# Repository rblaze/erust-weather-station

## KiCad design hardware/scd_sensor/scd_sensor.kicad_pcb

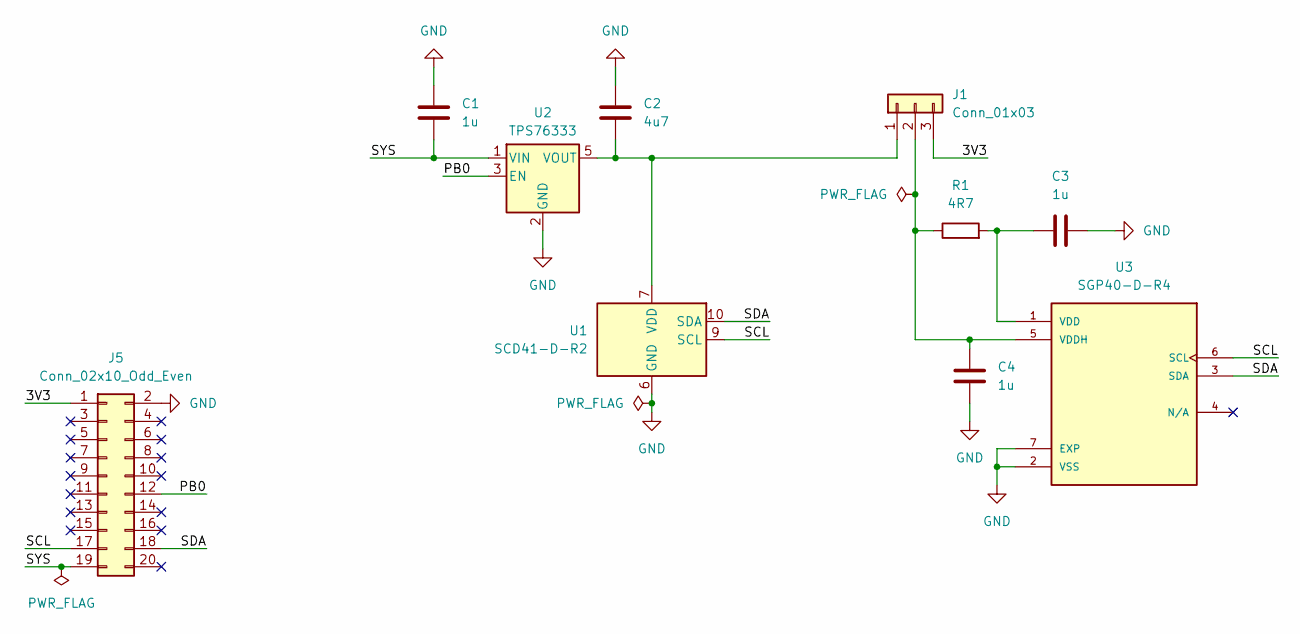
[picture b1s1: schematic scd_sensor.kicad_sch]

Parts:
C1, C3, C4: 1u; C_0402_1005Metric; JLCPCB C52923
C2: 4u7; C_0402_1005Metric; JLCPCB C23733
J1: Conn_01x03; PinHeader_1x03_P2.54mm_Vertical
J5: Conn_02x10_Odd_Even; PinHeader_2x10_P2.54mm_Vertical
R1: 4R7; R_0402_1005Metric; JLCPCB C23164
U1: SCD41-D-R2; Sensirion_SCD4x-1EP_10.1x10.1mm_P1.25mm_EP4.8x4.8mm; JLCPCB C3037696
U2: TPS76333; SOT-23-5
U3: SGP40-D-R4; XCDR_SGP40-D-R4; PARTREV 1.2; JLCPCB C2874215

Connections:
/3V3: J1.3, J5.1
/PB0: J5.12, U2.3 (EN)
/SCL: J5.17, U1.9 (SCL), U3.6 (SCL)
/SDA: J5.18, U1.10 (SDA), U3.3 (SDA)
/SYS: C1.2, J5.19, U2.1 (VIN)
GND: C1.1, C2.1, C3.2, C4.2, J5.2, U1.6 (GND), U1.20 (GND), U1.21 (GND), U2.2 (GND), U3.2 (VSS), U3.7 (EXP)
unnamed: C2.2, J1.1, U1.7 (VDD), U1.19 (VDD), U2.5 (VOUT)
unnamed: C4.1, J1.2, R1.1, U3.5 (VDDH)
unnamed: C3.1, R1.2, U3.1 (VDD)

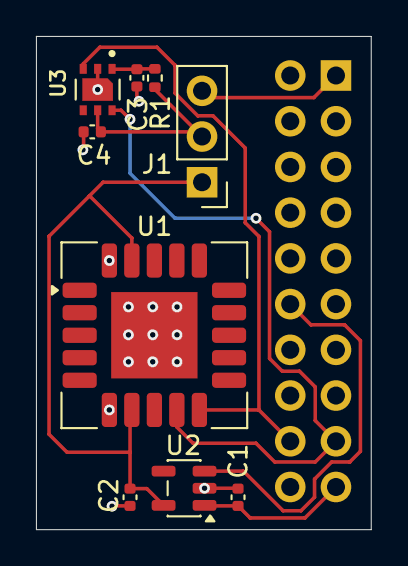
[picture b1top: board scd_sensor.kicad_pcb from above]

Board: 2 copper layers, 18.6 x 27.4 mm, 10 parts (1 on the bottom side), 9 nets.

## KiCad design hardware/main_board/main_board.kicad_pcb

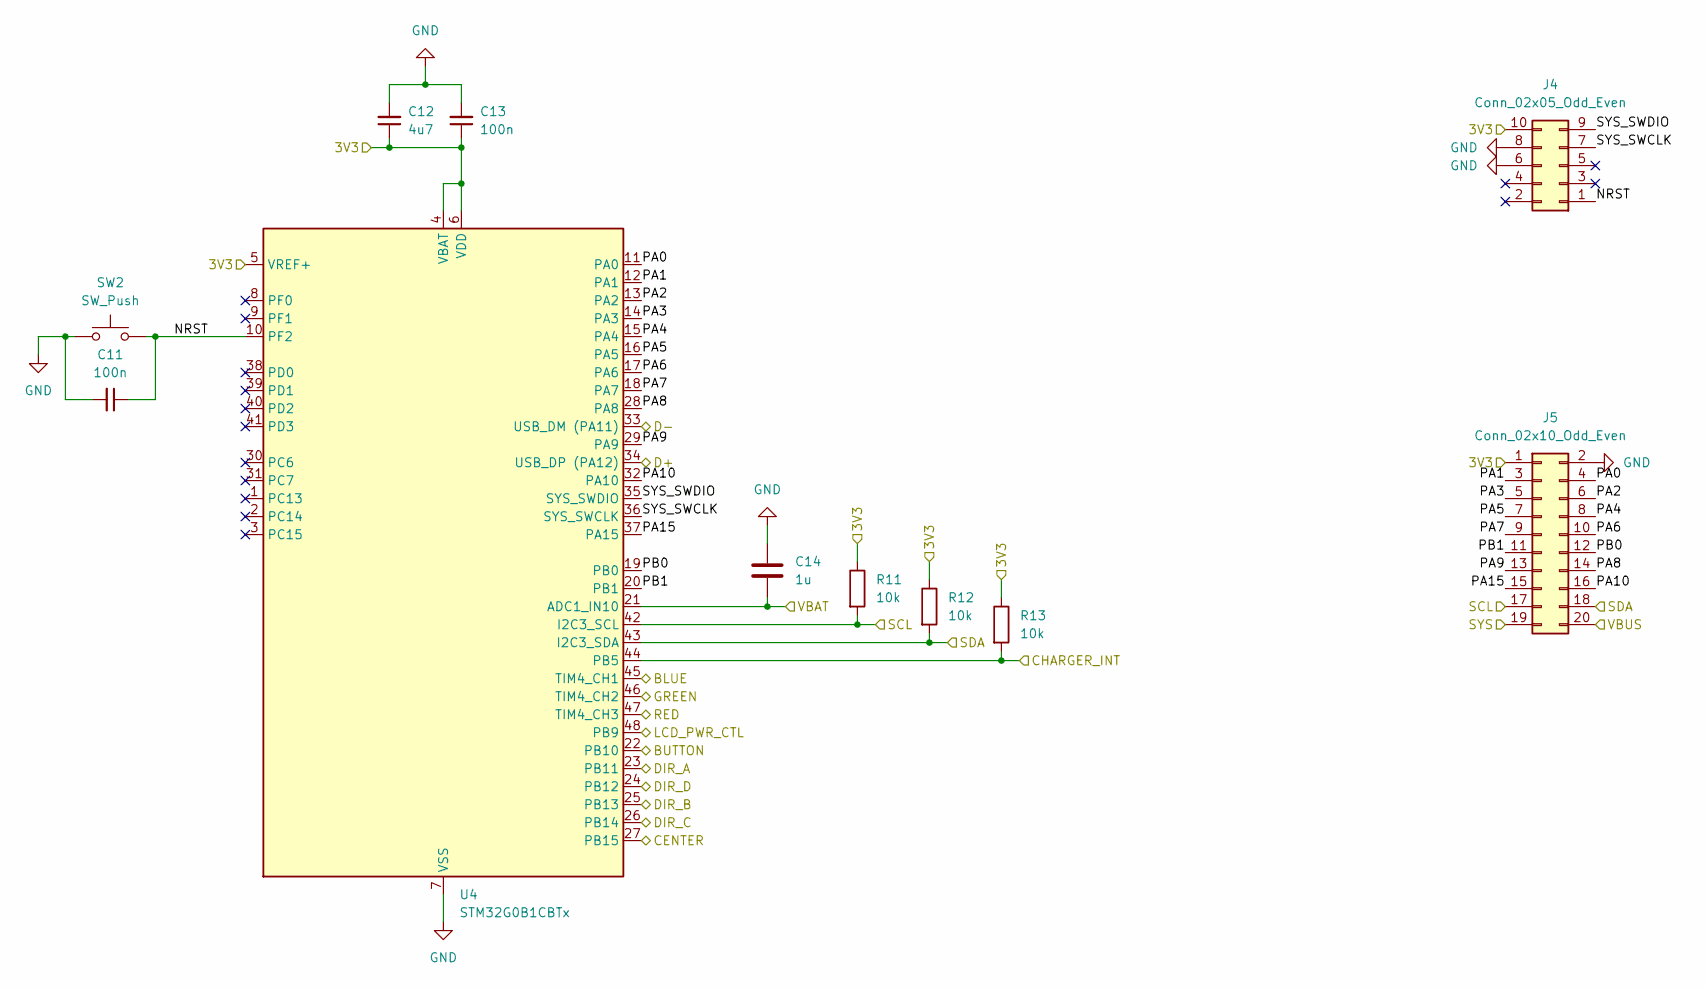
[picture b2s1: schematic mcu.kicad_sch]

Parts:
C11, C13: 100n; C_0402_1005Metric; JLCPCB C1525
C12: 4u7; C_0402_1005Metric; JLCPCB C23733
C14: 1u; C_0402_1005Metric; JLCPCB C52923
J4: Conn_02x05_Odd_Even; SAMTEC_FTSH-105-01-L-D-RA-K
J5: Conn_02x10_Odd_Even; SAMTEC_SSM-110-F-DH
R11, R12, R13: 10k; R_0402_1005Metric; JLCPCB C25744
SW2: SW_Push; SW_SPST_PTS810
U4: STM32G0B1CBTx; LQFP-48_7x7mm_P0.5mm; JLCPCB C2847904

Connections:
/MCU/3V3: C12.1, C13.1, J4.10, J5.1, R11.1, R12.1, R13.1, U4.4 (VBAT), U4.5 (VREF+), U4.6 (VDD); also elsewhere on the board
/MCU/BLUE: U4.45 (TIM4_CH1); also elsewhere on the board
/MCU/BUTTON: U4.22 (PB10); also elsewhere on the board
/MCU/CENTER: U4.27 (PB15); also elsewhere on the board
/MCU/CHARGER_INT: R13.2, U4.44 (PB5); also elsewhere on the board
/MCU/D+: U4.34 (USB_DP (PA12)); also elsewhere on the board
/MCU/D-: U4.33 (USB_DM (PA11)); also elsewhere on the board
/MCU/DIR_A: U4.23 (PB11); also elsewhere on the board
/MCU/DIR_B: U4.25 (PB13); also elsewhere on the board
/MCU/DIR_C: U4.26 (PB14); also elsewhere on the board
/MCU/DIR_D: U4.24 (PB12); also elsewhere on the board
/MCU/GREEN: U4.46 (TIM4_CH2); also elsewhere on the board
/MCU/LCD_PWR_CTL: U4.48 (PB9); also elsewhere on the board
/MCU/NRST: C11.1, J4.1, SW2.2, U4.10 (PF2)
/MCU/PA0: J5.4, U4.11 (PA0)
/MCU/PA1: J5.3, U4.12 (PA1)
/MCU/PA2: J5.6, U4.13 (PA2)
/MCU/PA3: J5.5, U4.14 (PA3)
/MCU/PA4: J5.8, U4.15 (PA4)
/MCU/PA5: J5.7, U4.16 (PA5)
/MCU/PA6: J5.10, U4.17 (PA6)
/MCU/PA7: J5.9, U4.18 (PA7)
/MCU/PA8: J5.14, U4.28 (PA8)
/MCU/PA9: J5.13, U4.29 (PA9)
/MCU/PA10: J5.16, U4.32 (PA10)
/MCU/PA15: J5.15, U4.37 (PA15)
/MCU/PB0: J5.12, U4.19 (PB0)
/MCU/PB1: J5.11, U4.20 (PB1)
/MCU/RED: U4.47 (TIM4_CH3); also elsewhere on the board
/MCU/SCL: J5.17, R11.2, U4.42 (I2C3_SCL); also elsewhere on the board
/MCU/SDA: J5.18, R12.2, U4.43 (I2C3_SDA); also elsewhere on the board
/MCU/SYS_SWCLK: J4.7, U4.36 (SYS_SWCLK)
/MCU/SYS_SWDIO: J4.9, U4.35 (SYS_SWDIO)
/MCU/VBAT: C14.2, U4.21 (ADC1_IN10); also elsewhere on the board
/MCU/VBUS: J5.20; also elsewhere on the board
/Power/SYS: J5.19; also elsewhere on the board
GND: C11.2, C12.2, C13.2, C14.1, J4.6, J4.8, J5.2, SW2.1, U4.7 (VSS); also elsewhere on the board

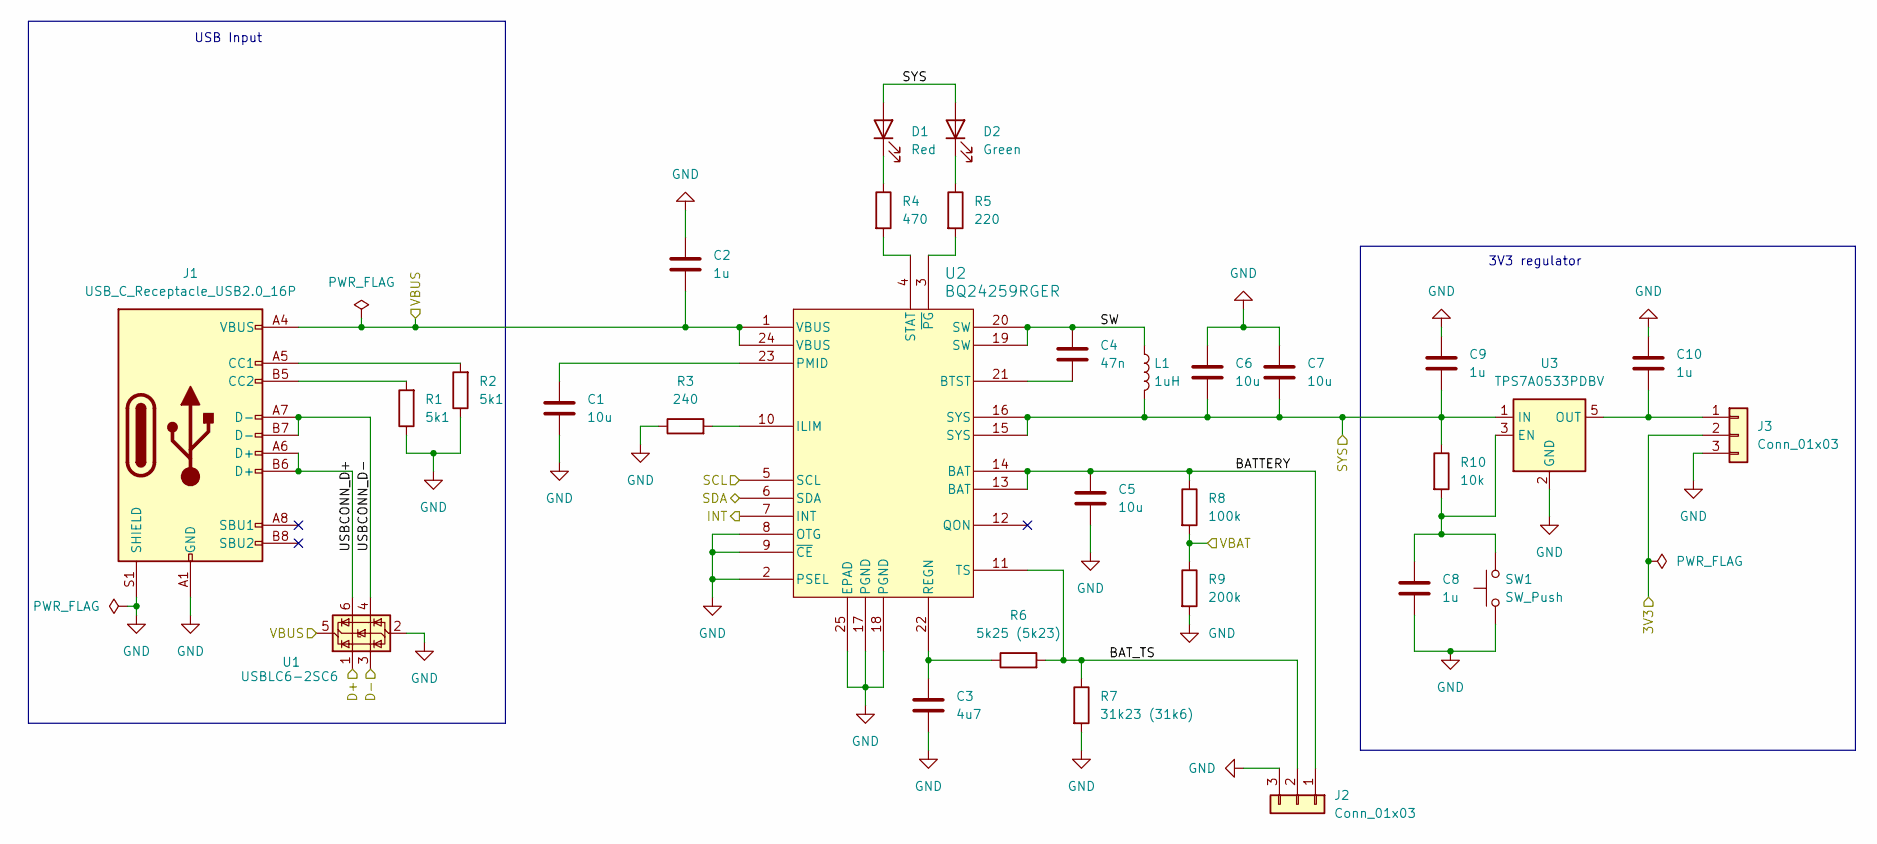
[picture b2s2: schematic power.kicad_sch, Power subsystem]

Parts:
C1, C5, C6, C7: 10u; C_0603_1608Metric; JLCPCB C19702
C2, C8, C9, C10: 1u; C_0402_1005Metric; JLCPCB C52923
C3: 4u7; C_0402_1005Metric; JLCPCB C23733
C4: 47n; C_0402_1005Metric; JLCPCB C384812
D1: Red; LED_0805_2012Metric; JLCPCB C2286
D2: Green; LED_0805_2012Metric; JLCPCB C72043
J1: USB_C_Receptacle_USB2.0_16P; USB_C_Receptacle_GCT_USB4105-xx-A_16P_TopMnt_Horizontal; JLCPCB C165948
J2: Conn_01x03; JST_PH_S3B-PH-SM4-TB_1x03-1MP_P2.00mm_Horizontal
J3: Conn_01x03; Harwin_M20-89003xx_1x03_P2.54mm_Horizontal
L1: 1uH; L_Murata_DFE201610P; JLCPCB C161082
R1, R2: 5k1; R_0402_1005Metric; JLCPCB C25905
R3: 240; R_0402_1005Metric; JLCPCB C25091
R4: 470; R_0402_1005Metric; JLCPCB C25117
R5: 220; R_0402_1005Metric; JLCPCB C25091
R6: 5k25 (5k23); R_0402_1005Metric; JLCPCB C852857
R7: 31k23 (31k6); R_0402_1005Metric; JLCPCB C852720
R8: 100k; R_0402_1005Metric; JLCPCB C25741
R9: 200k; R_0402_1005Metric; JLCPCB C25764
R10: 10k; R_0402_1005Metric; JLCPCB C25744
SW1: SW_Push; SW_SPST_PTS810
U1: USBLC6-2SC6; SOT-23-6; JLCPCB C7519
U2: BQ24259RGER; RGE24_2P7X2P7_TEX; JLCPCB C473366
U3: TPS7A0533PDBV; SOT-23-5; JLCPCB C2862740

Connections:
/MCU/3V3: J3.2; also elsewhere on the board
/MCU/CHARGER_INT: U2.7 (INT); also elsewhere on the board
/MCU/D+: U1.1 (I/O1); also elsewhere on the board
/MCU/D-: U1.3 (I/O2); also elsewhere on the board
/MCU/SCL: U2.5 (SCL); also elsewhere on the board
/MCU/SDA: U2.6 (SDA); also elsewhere on the board
/MCU/VBAT: R8.2, R9.1; also elsewhere on the board
/MCU/VBUS: C2.2, J1.A4 (VBUS), J1.A9 (VBUS), J1.B4 (VBUS), J1.B9 (VBUS), U1.5 (VBUS), U2.1 (VBUS), U2.24 (VBUS); also elsewhere on the board
/Power/BATTERY: C5.1, J2.1, R8.1, U2.13 (BAT), U2.14 (BAT)
/Power/BAT_TS: J2.2, R6.2, R7.1, U2.11 (TS)
/Power/SW: C4.1, L1.1, U2.19 (SW), U2.20 (SW)
/Power/SYS: C6.2, C7.2, C9.2, D1.2 (A), D2.2 (A), L1.2, R10.1, U2.15 (SYS), U2.16 (SYS), U3.1 (IN); also elsewhere on the board
/Power/USBCONN_D+: J1.A6 (D+), J1.B6 (D+), U1.6 (I/O1)
/Power/USBCONN_D-: J1.A7 (D-), J1.B7 (D-), U1.4 (I/O2)
GND: C1.2, C2.1, C3.2, C5.2, C6.1, C7.1, C8.2, C9.1, C10.1, J1.A1 (GND), J1.A12 (GND), J1.B1 (GND), J1.B12 (GND), J1.S1 (SHIELD), J2.3, J3.3, R1.1, R2.1, R3.1, R7.2, R9.2, SW1.1, U1.2 (GND), U2.2 (PSEL), U2.8 (OTG), U2.9 (~CE), U2.17 (PGND), U2.18 (PGND), U2.25 (EPAD), U2.V, U3.2 (GND); also elsewhere on the board
unnamed: D1.1 (K), R4.1
unnamed: D2.1 (K), R5.1
unnamed: J1.A5 (CC1), R2.2
unnamed: J1.B5 (CC2), R1.2
unnamed: C10.2, J3.1, U3.5 (OUT)
unnamed: C4.2, U2.21 (BTST)
unnamed: R3.2, U2.10 (ILIM)
unnamed: C1.1, U2.23 (PMID)
unnamed: C3.1, R6.1, U2.22 (REGN)
unnamed: R4.2, U2.4 (STAT)
unnamed: R5.2, U2.3 (~PG)
unnamed: C8.1, R10.2, SW1.2, U3.3 (EN)

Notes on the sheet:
3V3 regulator
USB Input

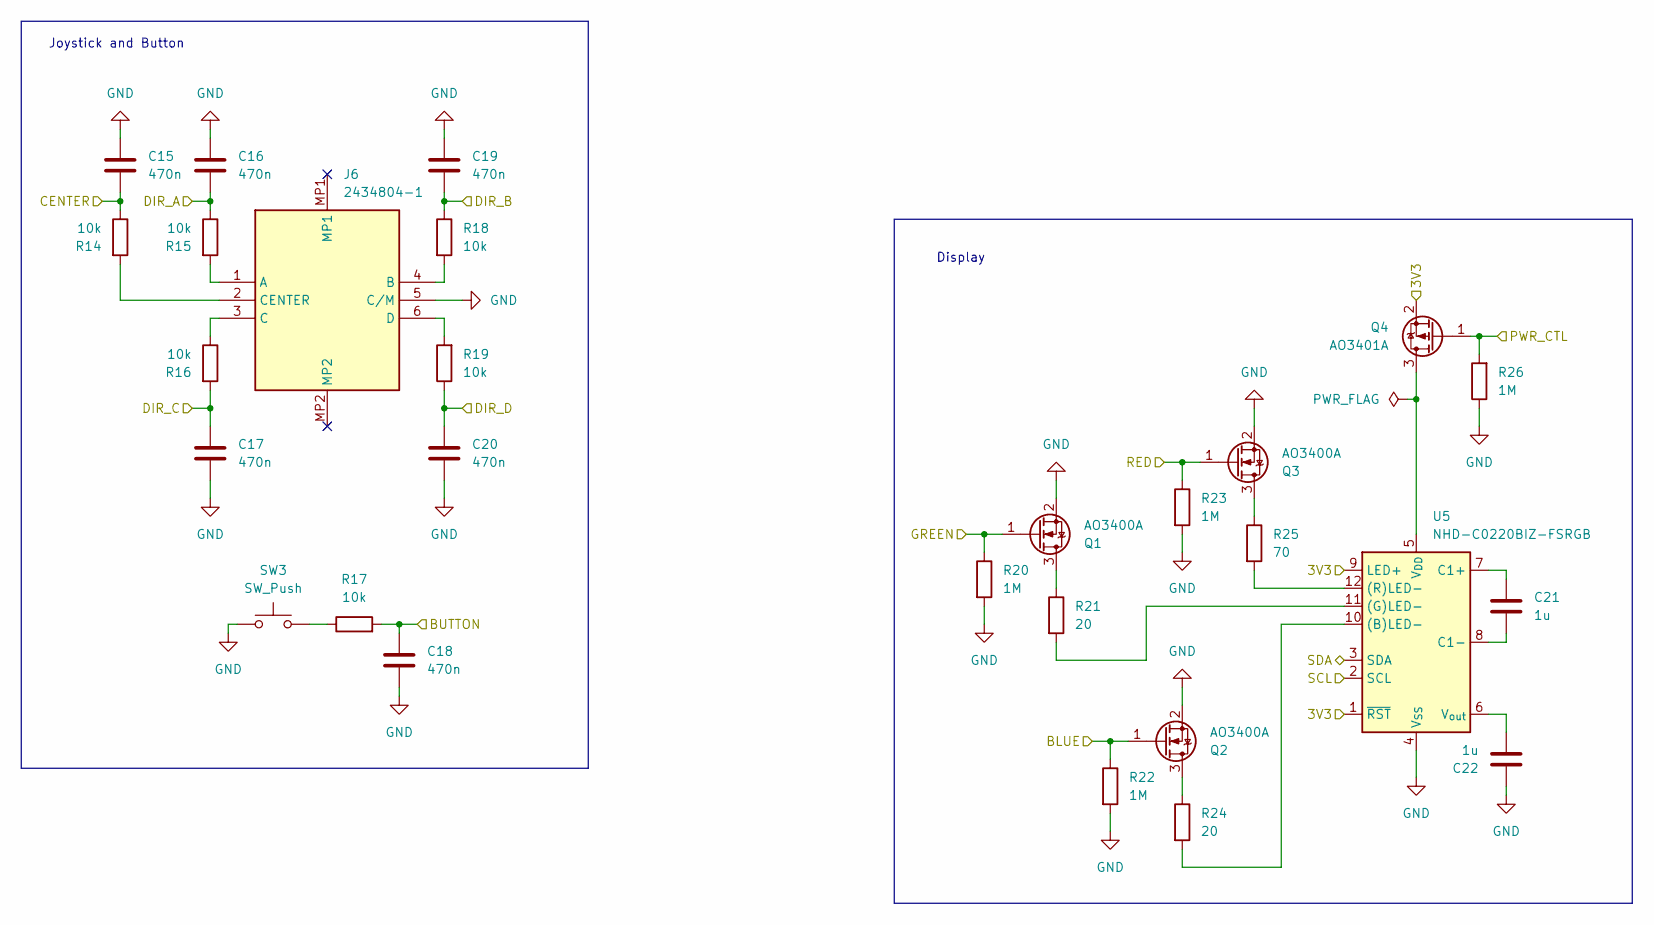
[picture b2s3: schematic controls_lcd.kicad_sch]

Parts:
C15, C16, C17, C18, C19, C20: 470n; C_0402_1005Metric; JLCPCB C47339
C21, C22: 1u; C_0402_1005Metric; JLCPCB C52923
J6: 2434804-1; TE_24348041; Manufacturer_Part_Number 2434804-1
Q1, Q2, Q3: AO3400A; SOT-23; JLCPCB C22469448
Q4: AO3401A; SOT-23; JLCPCB C28646269
R14, R15, R16, R17, R18, R19: 10k; R_0402_1005Metric; JLCPCB C25744
R20, R22, R23, R26: 1M; R_0402_1005Metric; JLCPCB C26083
R21, R24: 20; R_0402_1005Metric; JLCPCB C25092
R25: 70; R_0402_1005Metric; JLCPCB C25133
SW3: SW_Push; SW_SPST_PTS810
U5: NHD-C0220BIZ-FSRGB; NHD-C0220BiZ-FSRGB_no_mount

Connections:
/MCU/3V3: Q4.2 (S), U5.1 (~RST), U5.9 (LED+); also elsewhere on the board
/MCU/BLUE: Q2.1 (G), R22.1; also elsewhere on the board
/MCU/BUTTON: C18.1, R17.2; also elsewhere on the board
/MCU/CENTER: C15.1, R14.1; also elsewhere on the board
/MCU/DIR_A: C16.1, R15.1; also elsewhere on the board
/MCU/DIR_B: C19.1, R18.1; also elsewhere on the board
/MCU/DIR_C: C17.2, R16.2; also elsewhere on the board
/MCU/DIR_D: C20.2, R19.1; also elsewhere on the board
/MCU/GREEN: Q1.1 (G), R20.1; also elsewhere on the board
/MCU/LCD_PWR_CTL: Q4.1 (G), R26.2; also elsewhere on the board
/MCU/RED: Q3.1 (G), R23.1; also elsewhere on the board
/MCU/SCL: U5.2 (SCL); also elsewhere on the board
/MCU/SDA: U5.3 (SDA); also elsewhere on the board
GND: C15.2, C16.2, C17.1, C18.2, C19.2, C20.1, C22.1, J6.5 (C/M), Q1.2 (S), Q2.2 (S), Q3.2 (S), R20.2, R22.2, R23.2, R26.1, SW3.2, U5.4 (V_{SS}); also elsewhere on the board
unnamed: J6.1 (A), R15.2
unnamed: J6.4 (B), R18.2
unnamed: J6.3 (C), R16.1
unnamed: J6.2 (CENTER), R14.2
unnamed: J6.6 (D), R19.2
unnamed: Q1.3 (D), R21.1
unnamed: Q2.3 (D), R24.1
unnamed: Q3.3 (D), R25.1
unnamed: Q4.3 (D), U5.5 (V_{DD})
unnamed: R17.1, SW3.1
unnamed: R24.2, U5.10 ((B)LED-)
unnamed: R21.2, U5.11 ((G)LED-)
unnamed: R25.2, U5.12 ((R)LED-)
unnamed: C21.1, U5.7 (C1+)
unnamed: C21.2, U5.8 (C1-)
unnamed: C22.2, U5.6 (V_{out})

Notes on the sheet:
Display
Joystick and Button

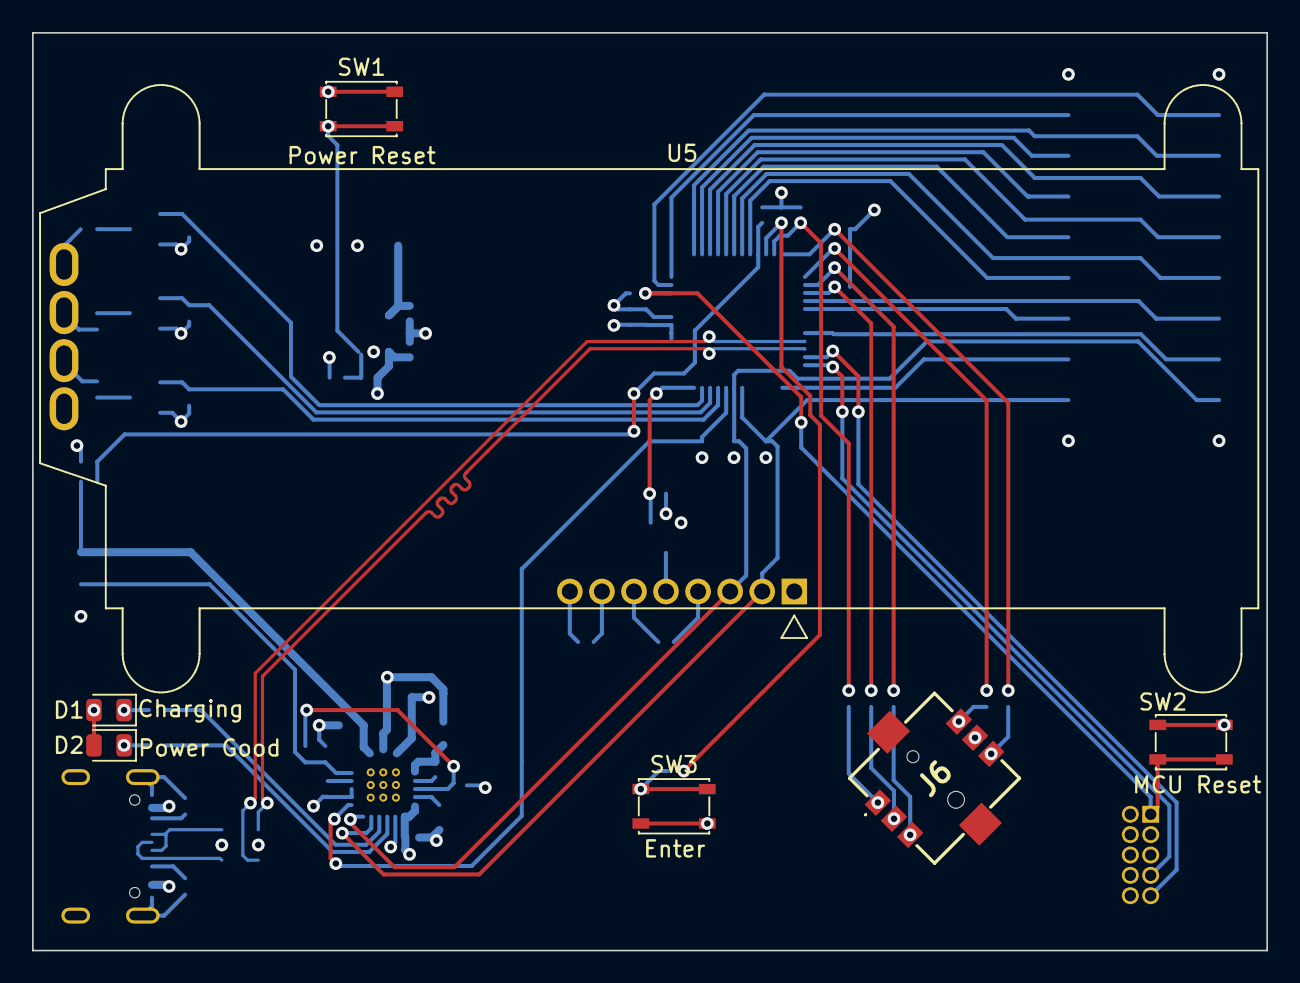
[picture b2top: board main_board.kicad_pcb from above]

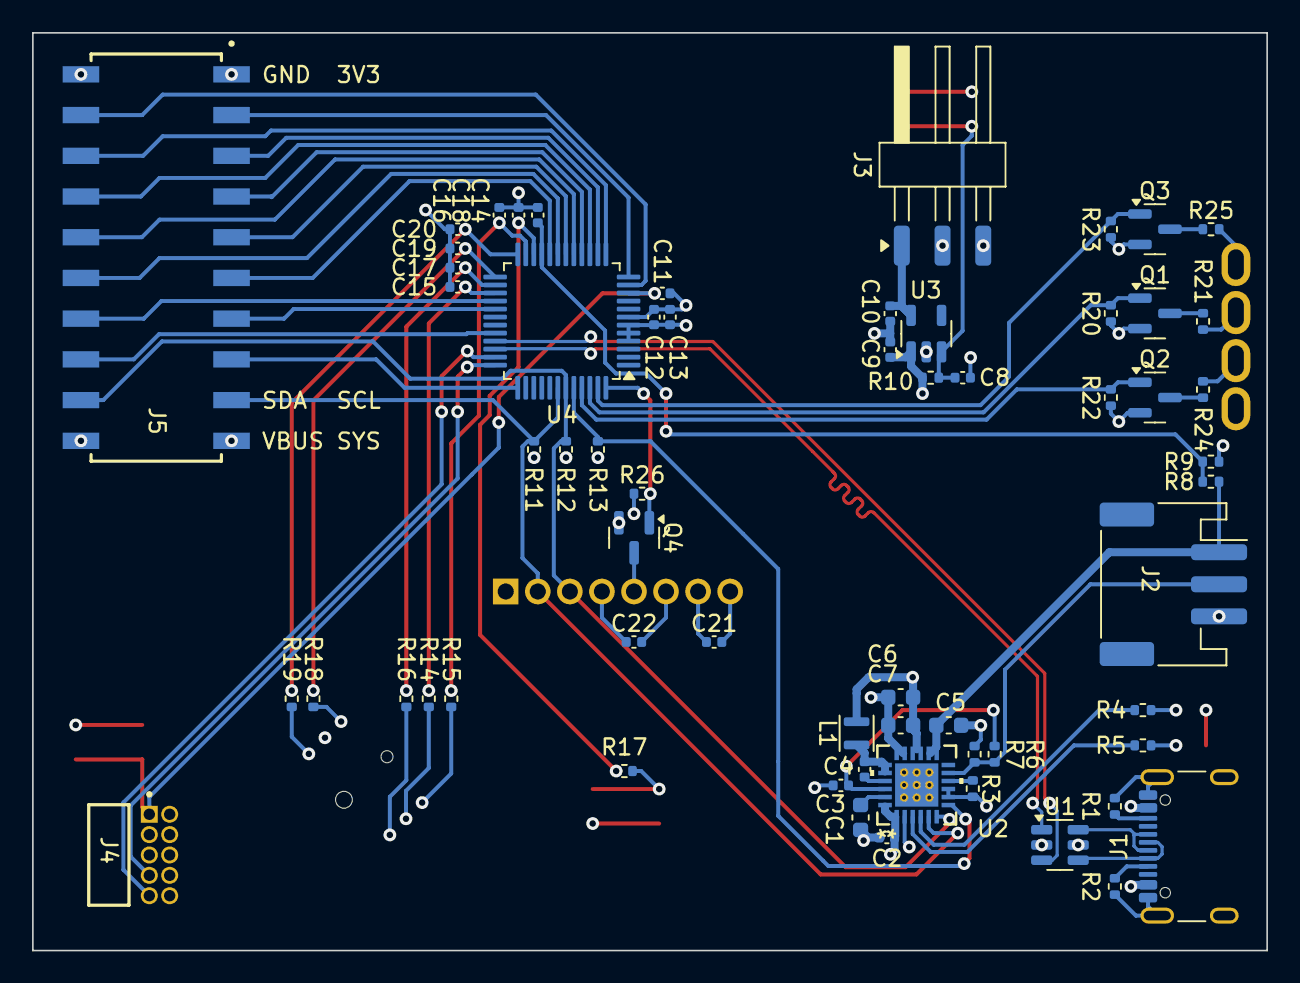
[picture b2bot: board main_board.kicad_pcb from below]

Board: 4 copper layers, 77.0 x 57.2 mm, 69 parts (62 on the bottom side), 70 nets.

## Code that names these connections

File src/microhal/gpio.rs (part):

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
gpio!(GPIOA, gpioa, pa, [
    // Pin: (pin, default_mode, bits...)
    PA0:  (pa0,  Analog, idr0,  odr0,  bs0,  br0,  moder0,  pupdr0,  ot0,  afrl,  afrel0, AF_A_L, exticr1, exti0_7,   tr0,  tr0),
    PA1:  (pa1,  Analog, idr1,  odr1,  bs1,  br1,  moder1,  pupdr1,  ot1,  afrl,  afrel1, AF_A_L, exticr1, exti8_15,  tr1,  tr1),
    PA2:  (pa2,  Analog, idr2,  odr2,  bs2,  br2,  moder2,  pupdr2,  ot2,  afrl,  afrel2, AF_A_L, exticr1, exti16_23, tr2,  tr2),
    PA3:  (pa3,  Analog, idr3,  odr3,  bs3,  br3,  moder3,  pupdr3,  ot3,  afrl,  afrel3, AF_A_L, exticr1, exti24_31, tr3,  tr3),
    PA4:  (pa4,  Analog, idr4,  odr4,  bs4,  br4,  moder4,  pupdr4,  ot4,  afrl,  afrel4, AF_A_L, exticr2, exti0_7,   tr4,  tr4),
    PA5:  (pa5,  Analog, idr5,  odr5,  bs5,  br5,  moder5,  pupdr5,  ot5,  afrl,  afrel5, AF_A_L, exticr2, exti8_15,  tr5,  tr5),
    PA6:  (pa6,  Analog, idr6,  odr6,  bs6,  br6,  moder6,  pupdr6,  ot6,  afrl,  afrel6, AF_A_L, exticr2, exti16_23, tr6,  tr6),
    PA7:  (pa7,  Analog, idr7,  odr7,  bs7,  br7,  moder7,  pupdr7,  ot7,  afrl,  afrel7, AF_A_L, exticr2, exti24_31, tr7,  tr7),
    PA8:  (pa8,  Analog, idr8,  odr8,  bs8,  br8,  moder8,  pupdr8,  ot8,  afrh,  afrel8, AF_A_H, exticr3, exti0_7,   tr8,  tr8),
    PA9:  (pa9,  Analog, idr9,  odr9,  bs9,  br9,  moder9,  pupdr9,  ot9,  afrh,  afrel9, AF_A_H, exticr3, exti8_15,  tr9,  tr9),
    PA10: (pa10, Analog, idr10, odr10, bs10, br10, moder10, pupdr10, ot10, afrh, afrel10, AF_A_H, exticr3, exti16_23, tr10, tr10),
    PA11: (pa11, Analog, idr11, odr11, bs11, br11, moder11, pupdr11, ot11, afrh, afrel11, AF_A_H, exticr3, exti24_31, tr11, tr11),
    PA12: (pa12, Analog, idr12, odr12, bs12, br12, moder12, pupdr12, ot12, afrh, afrel12, AF_A_H, exticr4, exti0_7,   tr12, tr12),
    PA13: (pa13, Alternate<0>, idr13, odr13, bs13, br13, moder13, pupdr13, ot13, afrh, afrel13, AF_A_H, exticr4, exti8_15,  tr13, tr13),
    PA14: (pa14, Alternate<0>, idr14, odr14, bs14, br14, moder14, pupdr14, ot14, afrh, afrel14, AF_A_H, exticr4, exti16_23, tr14, tr14),
    PA15: (pa15, Analog, idr15, odr15, bs15, br15, moder15, pupdr15, ot15, afrh, afrel15, AF_A_H, exticr4, exti24_31, tr15, tr15),
]);

gpio!(GPIOB, gpiob, pb, [
    // Pin: (pin, default_mode, bits...)
    PB0:  (pb0,  Analog, idr0,  odr0,  bs0,  br0,  moder0,  pupdr0,  ot0,  afrl,  afrel0, AF_B_L, exticr1, exti0_7,   tr0,  tr0),
    PB1:  (pb1,  Analog, idr1,  odr1,  bs1,  br1,  moder1,  pupdr1,  ot1,  afrl,  afrel1, AF_B_L, exticr1, exti8_15,  tr1,  tr1),
    PB2:  (pb2,  Analog, idr2,  odr2,  bs2,  br2,  moder2,  pupdr2,  ot2,  afrl,  afrel2, AF_B_L, exticr1, exti16_23, tr2,  tr2),
    PB3:  (pb3,  Analog, idr3,  odr3,  bs3,  br3,  moder3,  pupdr3,  ot3,  afrl,  afrel3, AF_B_L, exticr1, exti24_31, tr3,  tr3),
    PB4:  (pb4,  Analog, idr4,  odr4,  bs4,  br4,  moder4,  pupdr4,  ot4,  afrl,  afrel4, AF_B_L, exticr2, exti0_7,   tr4,  tr4),
    PB5:  (pb5,  Analog, idr5,  odr5,  bs5,  br5,  moder5,  pupdr5,  ot5,  afrl,  afrel5, AF_B_L, exticr2, exti8_15,  tr5,  tr5),
    PB6:  (pb6,  Analog, idr6,  odr6,  bs6,  br6,  moder6,  pupdr6,  ot6,  afrl,  afrel6, AF_B_L, exticr2, exti16_23, tr6,  tr6),
    PB7:  (pb7,  Analog, idr7,  odr7,  bs7,  br7,  moder7,  pupdr7,  ot7,  afrl,  afrel7, AF_B_L, exticr2, exti24_31, tr7,  tr7),
    PB8:  (pb8,  Analog, idr8,  odr8,  bs8,  br8,  moder8,  pupdr8,  ot8,  afrh,  afrel8, AF_B_H, exticr3, exti0_7,   tr8,  tr8),
    PB9:  (pb9,  Analog, idr9,  odr9,  bs9,  br9,  moder9,  pupdr9,  ot9,  afrh,  afrel9, AF_B_H, exticr3, exti8_15,  tr9,  tr9),
    PB10: (pb10, Analog, idr10, odr10, bs10, br10, moder10, pupdr10, ot10, afrh, afrel10, AF_B_H, exticr3, exti16_23, tr10, tr10),
    PB11: (pb11, Analog, idr11, odr11, bs11, br11, moder11, pupdr11, ot11, afrh, afrel11, AF_B_H, exticr3, exti24_31, tr11, tr11),
    PB12: (pb12, Analog, idr12, odr12, bs12, br12, moder12, pupdr12, ot12, afrh, afrel12, AF_B_H, exticr4, exti0_7,   tr12, tr12),
    PB13: (pb13, Analog, idr13, odr13, bs13, br13, moder13, pupdr13, ot13, afrh, afrel13, AF_B_H, exticr4, exti8_15,  tr13, tr13),
    PB14: (pb14, Analog, idr14, odr14, bs14, br14, moder14, pupdr14, ot14, afrh, afrel14, AF_B_H, exticr4, exti16_23, tr14, tr14),
    PB15: (pb15, Analog, idr15, odr15, bs15, br15, moder15, pupdr15, ot15, afrh, afrel15, AF_B_H, exticr4, exti24_31, tr15, tr15),
]);

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
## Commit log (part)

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2023-10-05 Initial program
2023-10-10 Measure LSI clock frequency.
2023-10-12 Do reliable reads of current tick count.
2023-10-15 Move LCD driver to a crate
2023-10-16 Prevent hanging at startup in release mode
2023-10-23 Add kicad project for main board
    rblaze/issue_tracker#5
2024-03-18 Make LCD independent from I2C bus implementation
2024-03-18 Fix bug in data copy
2024-03-18 Bump rtt-target from 0.4.0 to 0.5.0
    Bumps [rtt-target](https://github.com/probe-rs/rtt-target) from 0.4.0 to 0.5.0.
    - [Release notes](https://github.com/probe-rs/rtt-target/releases)
    - [Commits](https://github.com/probe-rs/rtt-target/compare/v0.4.0...v0.5.0)
    ---
    updated-dependencies:
    - dependency-name: rtt-target
2024-03-21 Make clippy happy
2024-04-04 Add navigation buttons
2024-04-04 Add charger control
2024-04-07 Add rudimental display naigation
2024-04-11 Fix LPTIM reload process.
    LPTIM is finicky and gets stuck if CMP value is reloaded too fast,
    CMPOK isn't cleared immediatelly or for other reasons. This version
    of code works, though it behaves weirdly too if HSI is not divided.
2024-04-22 Switch to LQFP chip
2024-04-22 Use embedded-hal 1.0 API in main
2024-04-24 Power cycle display on error
2024-04-29 Bump embedded-hal-bus from 0.1.0 to 0.2.0 (#5)
    Bumps [embedded-hal-bus](https://github.com/rust-embedded/embedded-hal) from 0.1.0 to 0.2.0.
    - [Release notes](https://github.com/rust-embedded/embedded-hal/releases)
    - [Changelog](https://github.com/rust-embedded/embedded-hal/blob/v0.2.0/CHANGELOG.md)
    - [Commits](https://github.com/rust-embedded/embedded-hal/compare/embedded-hal-bus-v0.1.0...v0.2.0)
    ---
    updated-dependencies:
2024-05-06 Update dependencies
2024-05-22 Add microhal with lptimer
2024-05-22 Add LPTIM1 support
2024-05-22 Refactor timer API
2024-05-28 Basic GPIO implementation
2024-06-05 Implement PWM in microhal
2024-06-07 Simplify Board struct
2024-08-20 Suppress warnings
2024-08-20 Bump portable-atomic from 1.6.0 to 1.7.0 (#6)
2024-09-16 Bump once_cell from 1.19.0 to 1.20.0
    Bumps [once_cell](https://github.com/matklad/once_cell) from 1.19.0 to 1.20.0.
    - [Changelog](https://github.com/matklad/once_cell/blob/master/CHANGELOG.md)
    - [Commits](https://github.com/matklad/once_cell/compare/v1.19.0...v1.20.0)
    ---
    updated-dependencies:
    - dependency-name: once_cell
2024-09-30 Bump portable-atomic from 1.8.0 to 1.9.0
    Bumps [portable-atomic](https://github.com/taiki-e/portable-atomic) from 1.8.0 to 1.9.0.
    - [Release notes](https://github.com/taiki-e/portable-atomic/releases)
    - [Changelog](https://github.com/taiki-e/portable-atomic/blob/main/CHANGELOG.md)
    - [Commits](https://github.com/taiki-e/portable-atomic/compare/v1.8.0...v1.9.0)
    ---
    updated-dependencies:
2024-09-30 Bump once_cell from 1.19.0 to 1.20.1
    Bumps [once_cell](https://github.com/matklad/once_cell) from 1.19.0 to 1.20.1.
    - [Changelog](https://github.com/matklad/once_cell/blob/master/CHANGELOG.md)
    - [Commits](https://github.com/matklad/once_cell/compare/v1.19.0...v1.20.1)
    ---
    updated-dependencies:
    - dependency-name: once_cell
2024-10-07 Bump once_cell from 1.20.1 to 1.20.2 (#13)
    Bumps [once_cell](https://github.com/matklad/once_cell) from 1.20.1 to 1.20.2.
    - [Changelog](https://github.com/matklad/once_cell/blob/master/CHANGELOG.md)
    - [Commits](https://github.com/matklad/once_cell/compare/v1.20.1...v1.20.2)
    ---
    updated-dependencies:
    - dependency-name: once_cell
2024-10-08 Update display and joystick pins
2024-10-22 Add I2C support
2024-10-27 Minor code cleanup
2024-10-28 Fix EXTI event names
2024-11-01 cargo update
2024-11-02 Move microhal to its own crate
2024-11-06 Move all peripherals to port B
2024-11-25 Bump rtt-target from 0.5.0 to 0.6.0
    Bumps [rtt-target](https://github.com/probe-rs/rtt-target) from 0.5.0 to 0.6.0.
    - [Release notes](https://github.com/probe-rs/rtt-target/releases)
    - [Commits](https://github.com/probe-rs/rtt-target/compare/v0.5.0...rtt-target-v0.6.0)
    ---
    updated-dependencies:
    - dependency-name: rtt-target
2024-12-09 Bump stm32g0-hal from `390c4a3` to `f3c2507`
    Bumps [stm32g0-hal](https://github.com/rblaze/erust-stm32g0-hal) from `390c4a3` to `f3c2507`.
    - [Commits](https://github.com/rblaze/erust-stm32g0-hal/compare/390c4a337540c00da703a5b46e6397d88e46de72...f3c25070894787dfeb88ab539130e2afc6acb042)
    ---
    updated-dependencies:
    - dependency-name: stm32g0-hal
    dependency-type: direct:production
2024-12-09 Bump rtt-target from 0.6.0 to 0.6.1 (#18)
    Bumps [rtt-target](https://github.com/probe-rs/rtt-target) from 0.6.0 to 0.6.1.
    - [Release notes](https://github.com/probe-rs/rtt-target/releases)
    - [Commits](https://github.com/probe-rs/rtt-target/compare/rtt-target-v0.6.0...rtt-target-v0.6.1)
    ---
    updated-dependencies:
    - dependency-name: rtt-target
2024-12-31 Use interrupts to handle USB comms
2025-01-19 Extract USB support to module
2025-01-20 Remove serial LED
2025-01-20 Show latest faults register
2025-01-27 Bump embedded-hal-bus from 0.2.0 to 0.3.0 (#19)
    Bumps [embedded-hal-bus](https://github.com/rust-embedded/embedded-hal) from 0.2.0 to 0.3.0.
    - [Release notes](https://github.com/rust-embedded/embedded-hal/releases)
    - [Commits](https://github.com/rust-embedded/embedded-hal/compare/embedded-hal-bus-v0.2.0...embedded-hal-bus-v0.3.0)
    ---
    updated-dependencies:
    - dependency-name: embedded-hal-bus
2025-02-05 Update mainboard schematic to match breadboard
2025-02-06 Add daughter board connector
2025-02-11 Bump once_cell from 1.20.2 to 1.20.3 (#20)
    Bumps [once_cell](https://github.com/matklad/once_cell) from 1.20.2 to 1.20.3.
    - [Changelog](https://github.com/matklad/once_cell/blob/master/CHANGELOG.md)
    - [Commits](https://github.com/matklad/once_cell/compare/v1.20.2...v1.20.3)
    ---
    updated-dependencies:
    - dependency-name: once_cell
2025-02-27 Update to Rust edition 2024
2025-03-17 Bump once_cell from 1.20.3 to 1.21.1 (#21)
    Bumps [once_cell](https://github.com/matklad/once_cell) from 1.20.3 to 1.21.1.
    - [Changelog](https://github.com/matklad/once_cell/blob/master/CHANGELOG.md)
    - [Commits](https://github.com/matklad/once_cell/compare/v1.20.3...v1.21.1)
    ---
    updated-dependencies:
    - dependency-name: once_cell
2025-03-31 Bump once_cell from 1.21.1 to 1.21.3 (#22)
    Bumps [once_cell](https://github.com/matklad/once_cell) from 1.21.1 to 1.21.3.
    - [Changelog](https://github.com/matklad/once_cell/blob/master/CHANGELOG.md)
    - [Commits](https://github.com/matklad/once_cell/compare/v1.21.1...v1.21.3)
    ---
    updated-dependencies:
    - dependency-name: once_cell
2025-06-09 Bump portable-atomic from 1.11.0 to 1.11.1 (#23)
    Bumps [portable-atomic](https://github.com/taiki-e/portable-atomic) from 1.11.0 to 1.11.1.
    - [Release notes](https://github.com/taiki-e/portable-atomic/releases)
    - [Changelog](https://github.com/taiki-e/portable-atomic/blob/main/CHANGELOG.md)
    - [Commits](https://github.com/taiki-e/portable-atomic/compare/v1.11.0...v1.11.1)
    ---
    updated-dependencies:
2025-07-02 Fix PCB routing errors, update LED and connector footprints
2025-09-01 Correct orientation of the debug connector
2025-09-22 Add CO2 sensor board
2025-10-17 Add expansion socket markings
2025-11-10 Add SGP40 symbol and footprint
2025-11-16 Change plot settings
2025-12-15 Bump lcd from `acf31f1` to `810ffac`
    Bumps [lcd](https://github.com/rblaze/erust-lcd) from `acf31f1` to `810ffac`.
    - [Commits](https://github.com/rblaze/erust-lcd/compare/acf31f12fa99afe0da07ec47c3fa8035435c2784...810ffac5b9cbe57f2e67d41ff6dc216220aab72e)
    ---
    updated-dependencies:
    - dependency-name: lcd
    dependency-version: 810ffac5b9cbe57f2e67d41ff6dc216220aab72e
2025-12-22 Bump async-scheduler from `9371ef1` to `44c3c0e`
    Bumps [async-scheduler](https://github.com/rblaze/rust-async-scheduler) from `9371ef1` to `44c3c0e`.
    - [Commits](https://github.com/rblaze/rust-async-scheduler/compare/9371ef1a08f2ae8beb2959eba6410865dc3efcb0...44c3c0e3d0b40dc1ecd5bf2254cec20081b83d7b)
    ---
    updated-dependencies:
    - dependency-name: async-scheduler
    dependency-version: 44c3c0e3d0b40dc1ecd5bf2254cec20081b83d7b
2025-12-22 Bump async-scheduler from `9371ef1` to `44c3c0e` (#29)
    Bumps [async-scheduler](https://github.com/rblaze/rust-async-scheduler) from `9371ef1` to `44c3c0e`.
    - [Commits](https://github.com/rblaze/rust-async-scheduler/compare/9371ef1a08f2ae8beb2959eba6410865dc3efcb0...44c3c0e3d0b40dc1ecd5bf2254cec20081b83d7b)
    ---
    updated-dependencies:
    - dependency-name: async-scheduler
    dependency-version: 44c3c0e3d0b40dc1ecd5bf2254cec20081b83d7b
2025-12-22 Bump lcd from `acf31f1` to `810ffac` (#26)
    Bumps [lcd](https://github.com/rblaze/erust-lcd) from `acf31f1` to `810ffac`.
    - [Commits](https://github.com/rblaze/erust-lcd/compare/acf31f12fa99afe0da07ec47c3fa8035435c2784...810ffac5b9cbe57f2e67d41ff6dc216220aab72e)
    ---
    updated-dependencies:
    - dependency-name: lcd
    dependency-version: 810ffac5b9cbe57f2e67d41ff6dc216220aab72e
2025-12-29 Bump stm32g0-hal from `4e1fa02` to `df5f104`
    Bumps [stm32g0-hal](https://github.com/rblaze/erust-stm32g0-hal) from `4e1fa02` to `df5f104`.
    - [Commits](https://github.com/rblaze/erust-stm32g0-hal/compare/4e1fa02db2d1ff4270160a8260d4f205696f7fcd...df5f10438c90483c2cba48a23bb89a4def139048)
    ---
    updated-dependencies:
    - dependency-name: stm32g0-hal
    dependency-version: df5f10438c90483c2cba48a23bb89a4def139048
2025-12-30 Fix SDA/SCL placement on SGP40
2025-12-30 Remove obsolete file
2025-12-30 Remove unwanted footprints
2025-12-31 Deny unsafe_code by default
2026-01-03 Move charger watchdog task to a module
2026-01-05 Rewrite tasks to use state objects
2026-01-19 Bump thiserror from 2.0.17 to 2.0.18
    Bumps [thiserror](https://github.com/dtolnay/thiserror) from 2.0.17 to 2.0.18.
    - [Release notes](https://github.com/dtolnay/thiserror/releases)
    - [Commits](https://github.com/dtolnay/thiserror/compare/2.0.17...2.0.18)
    ---
    updated-dependencies:
    - dependency-name: thiserror
2026-01-20 Fix formatting
2026-02-01 Add 3D models for all mainboard components
2026-02-23 Bump futures from 0.3.31 to 0.3.32 (#37)
    Bumps [futures](https://github.com/rust-lang/futures-rs) from 0.3.31 to 0.3.32.
    - [Release notes](https://github.com/rust-lang/futures-rs/releases)
    - [Changelog](https://github.com/rust-lang/futures-rs/blob/master/CHANGELOG.md)
    - [Commits](https://github.com/rust-lang/futures-rs/compare/0.3.31...0.3.32)
    ---
    updated-dependencies:
2026-03-02 Refactor code to use trait-based board API.
    This will allow adding tests with simulated hardware.
2026-03-13 Enable IWDG to restart the firmware in case of transient errors
2026-03-20 Add history buffer to StationData
2026-03-26 Move time-related types to firmware crate
2026-03-29 Update github actions
2026-03-29 Move co2 module to firmware crate
2026-03-29 Move screen module to firmware crate
2026-03-29 Remove unneeded lint directives
2026-04-05 Increase charger watchdog timeout to 160 seconds.
    This allows to wake up device less often.
2026-04-06 Move board support modules to top level
    Now that firmware is in separate crate, there is no need for submodules.
